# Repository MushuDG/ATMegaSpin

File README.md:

> [!WARNING]  
> Hey! This project is still a Work in Progress. Files, instructions, and other stuff might change!

# Table of contents
1. [Goal of the game](#goal-of-the-game)
2. [PCB Pictures](#pcb-pictures)
    1. [Front](#front)
    2. [Back](#back)
3. [Schematics](#schematics)
    1. [Electrical schematic](#electrical-schematic)
    2. [PCB schematic](#pcb-schematic)
    3. [Mechanical schematic](#mechanical-schematic)
    4. [ATMega328P Pinout](#atmega328p-pinout)
4. [GERBER - 3D printed Files - Other Hardware stuff](#gerber---3d-printed-files---other-hardware-stuff)
    1. [3D Printed parts](#3d-printed-parts)
    2. [PCB GERBER File](#pcb-gerber-file)
    3. [Electrical parts](#electrical-parts)
5. [Installation](#installation)
    1. [Burn bootloader](#burn-bootloader)
        1. [Needed tools](#needed-tools)
        2. [Circuit](#circuit)
        3. [Pinout](#pinout)
        4. [Upload ISP sketch](#upload-isp-sketch)
        5. [Burn bootloader](#burn-bootloader-1)
            1. [Installing Mini-core](#installing-mini-core)
            2. [Select your device, crystal and programmer and burn bootloader](#select-your-device-crystal-and-programmer-and-burn-bootloader)
    2. [Upload sketch from programmer](#upload-sketch-from-programmer)
6. [Contributions](#contributions)
7. [License](#license)

# ATMegaSpin
## Goal of the game:
A LED game where the player has to press a button at the right moment to reach a specific goal. The challenge of the game lies in the speed at which the LEDs blink, the reduction of this speed with each achieved goal, and the necessity to press the button at the right moment to advance in the game.

## PCB Pictures:
### Front

### Back

# Schematics
## Electrical schematic:
[Electrical schematic](https://github.com/MushuDG/ATMegaSpin/blob/main/PDF/ATMegaSpin_Schematic.pdf)

## PCB schematic:
[PCB schematic](https://github.com/MushuDG/ATMegaSpin/blob/main/PDF/ATMegaSpin_PCB.pdf)

## Mechanical schematic:
[Mechanical schematic](https://github.com/MushuDG/ATMegaSpin/blob/main/PDF/EnsemblePCB.pdf)

## ATMega328P Pinout:
| Arduino Pinout | Electrical Part | ATMega328 Pinout | ATMega328 Pinout | Electrical Part | Arduino Pinout |
| -------------- | --------------- | ---------------- | ---------------- | --------------- | -------------- |
| Reset          | Not used        | 1                | 28               | Not used        | A5             |
| D0 RX          | Not used        | 2                | 27               | Not used        | A4             |
| D1 TX          | Not used        | 3                | 26               | Not used        | A3             |
| D2             | LED 1           | 4                | 25               | Not used        | A2             |
| D3             | Button Pin 4    | 5                | 24               | Not used        | A1             |
| D4             | LED 2           | 6                | 23               | Not used        | A0             |
| VCC            | +5V             | 7                | 22               | GND             | GND            |
| GND            | GND             | 8                | 21               | Not used        | Aref           |
| Crystal        | Crystal         | 9                | 20               | Not used        | Avcc           |
| Crystal        | Crystal         | 10               | 19               | LED 10          | D13            |
| D5             | Not used        | 11               | 18               | LED 9           | D12            |
| D6             | LED 3           | 12               | 17               | LED 8           | D11            |
| D7             | LED 4           | 13               | 16               | LED 7           | D10            |
| D8             | LED 5           | 14               | 15               | LED 6           | D9             |

# GERBER - 3D printed Files - Other Hardware stuff
## 3D Printed parts:
[3D Printed parts](https://www.printables.com/fr/model/649943-atmegaspin)

## PCB GERBER File:
[PCB GERBER File](https://github.com/MushuDG/ATMegaSpin/blob/main/KiCad/ATMegaSpin/ATMegaSpin-GERBER.zip)

## Electrical parts:
| N° | PRODUCTS DETAILS                                                                                | SUPPLIER | QUANTITY | PRICE       | TOTAL        |
| -- | ----------------------------------------------------------------------------------------------- | -------- | -------- | ----------- | ------------ |
| 1  | ED3050-5-ND‎<br>ED281DT‎<br>CONN IC DIP SOCKET 28POS TIN                                        | Digikey  | 5        | Fr. 0.40000 | Fr. 2.00000  |
| 2  | ATMEGA328P-PU-ND‎‎<br>ATMEGA328P-PU‎<br>IC MCU 8BIT 32KB FLASH 28DIP                            | Digikey  | 5        | Fr. 2.60000 | Fr. 13.00000 |
| 3  | 2223-TS02-66-60-BK-160-SCR-D-ND‎<br>TS02-66-60-BK-160-SCR-D‎<br>6 X 6 MM, 6 MM ACTUATOR HEIGHT, | Digikey  | 5        | Fr. 0.09000 | Fr. 0.45000  |
| 4  | 50-ECS-160-18-4X-CKM-ND‎<br>ECS-160-18-4X-CKM‎<br>CRYSTAL 16.0000MHZ 18PF TH                    | Digikey  | 5        | Fr. 0.41000 | Fr. 2.05000  |
| 5  | BC1005CT-ND‎<br>‎K220J15C0GF5TL2‎<br>CAP CER 22PF 50V C0G/NP0 RADIAL                            | Digikey  | 10       | Fr. 0.15500 | Fr. 1.55000  |
| 6  | BS-7-ND‎<br>BS-7‎<br>BATT HLDR COIN 20MM 1 CEL PC PIN                                           | Digikey  | 10       | Fr. 0.84100 | Fr. 8.41000  |
| 7  | CF18JT200RCT-ND‎<br>‎CF18JT200R‎<br>RES 200 OHM 5% 1/8W AXIAL                                   | Digikey  | 50       | Fr. 0.02260 | Fr. 1.13000  |
| 8  | ‎516-1325-ND‎<br>‎HLMP-4700‎<br>LED RED DIFFUSED T-1 3/4 T/H                                    | Digikey  | 50       | Fr. 0.34600 | Fr. 17.30000 |
| 9  | MFS101D-6-Z                                                                                     | Digikey  | 5        | Fr. 1.52000 | Fr. 7.60000  |
| 10 | PCB JLCPCB                                                                                      | JLCPCB   | 5        | Fr. 1.84000 | Fr. 9.20000  |
|    |                                                                                                 |          |          |             |              |
|    | Aprox. Total                                                                                    |          |          |             | Fr. 62.69    |
|    | Aprox. Total/pcs                                                                                |          |          |             | Fr. 12.54    |

# Prototype

# Installation
Before you can connect the [ATMega328P](https://en.wikipedia.org/wiki/ATmega328) microcontroller to the circuit, it's necessary to burn the bootloader of the chip. Once the bootloader is burned, the program can be uploaded to it.

*"To program the bootloader and provide to the microcontroller the compatibility with the Arduino Software (IDE) you need to use an In-circuit Serial Programmer (ISP) that is the device that connects to a specific set of pins of the microcontroller to perform the programming of the whole flash memory of the microcontroller, bootloader included. The ISP programming procedure also includes the writing of fuses: a special set of bits that define how the microcontroller works under specific circumstances."*

The Memory Map of an ATmega328P

> [!IMPORTANT]  
> The preceding paragraph and illustration were taken from this documentation: [Arduino as ISP and Arduino Bootloaders](https://docs.arduino.cc/built-in-examples/arduino-isp/ArduinoISP) -  Accessed on 2023-11-22

## Burn bootloader
### Needed tools
To burn the bootloader on the microcontroller you need 2 arduino (In this case I use Arduino UNO) cards. The first will be used as an ISP programmer.

### Circuit

### Pinout
| Arduino Programmer Pin | Arduino Target Pin |
| ---------------------- | ------------------ |
| +5 [V]                 | +5 [V]             |
| GND                    | GND                |
| D10                    | Reset              |
| 11                     | 11                 |
| 12                     | 12                 |
| 13                     | 13                 |

### Upload ISP sketch
Once the circuit is connected, follow the following instructions to apply the ISP programming sketch on the Arduino programmer:
1. Open the Arduino IDE and from the menu *File > Examples > 11.ArduinoISP > ArduinoISP*, load the sketch.
2. Select the proper board (I.E.: Arduino Uno) and upload the sketch

### Burn bootloader
#### Installing Mini-core
1. Open up the Arduino IDE and navigate to the preferences (or press ctrl+,). Copy the following URL into the empty field labelled *‘Additional Boards Manager URLs’*: [https://mcudude.github.io/MiniCore/package_MCUdude_MiniCore_index.json](https://mcudude.github.io/MiniCore/package_MCUdude_MiniCore_index.json)
2. Go to the boards manager, which can be found under *Tools > Board > Boards Manager*.
Type *‘minicore’* into the search bar and the relevant entry will appear. Select the latest version and click *‘install’*. Once the installation is complete, close the boards manager window.

#### Select your device, crystal and programmer and burn bootloader
1. Select the relevant device, crystal and programmer options under the *‘tools’* menu.
2. Under board, select *‘ATmega328’* (or whichever chip you’re using).
3. Under clock, select the frequency of your external clock. It should be written in block capitals on the top of the crystal’s casing.
4. Set your programmer as *‘Arduino as ISP’*
5. Burn the bootloader using the *‘Burn Bootloader’* option at the bottom of the Tools menu.

## Upload sketch from programmer
Once the bootloader is burned, open up the *[Spin.ino](https://github.com/MushuDG/ATMegaSpin/blob/main/Code/Spin/Spin.ino)* sketch. From the menu *Sketch* use the *Upload Using Programmer* tool to Upload the sketch to the ATMega328P Target.

Then, you can disconnect the MCU from the Arduino target and clip it to your circuit. 

## Contributions

Contributions to this project are welcome! If you have ideas for improvements or bug fixes, please follow the [contribution guidelines](CONTRIBUTING.md).

1. Fork the project.
2. Create your feature branch: `git checkout -b feature/AmazingFeature`.
3. Commit your changes: `git commit -m 'Add some amazing feature'`.
4. Push to the branch: `git push origin feature/AmazingFeature`.
5. Open a pull request.

## License

This project is licensed under the  AGPL-3.0 license - see the [LICENSE](LICENSE) file for details.

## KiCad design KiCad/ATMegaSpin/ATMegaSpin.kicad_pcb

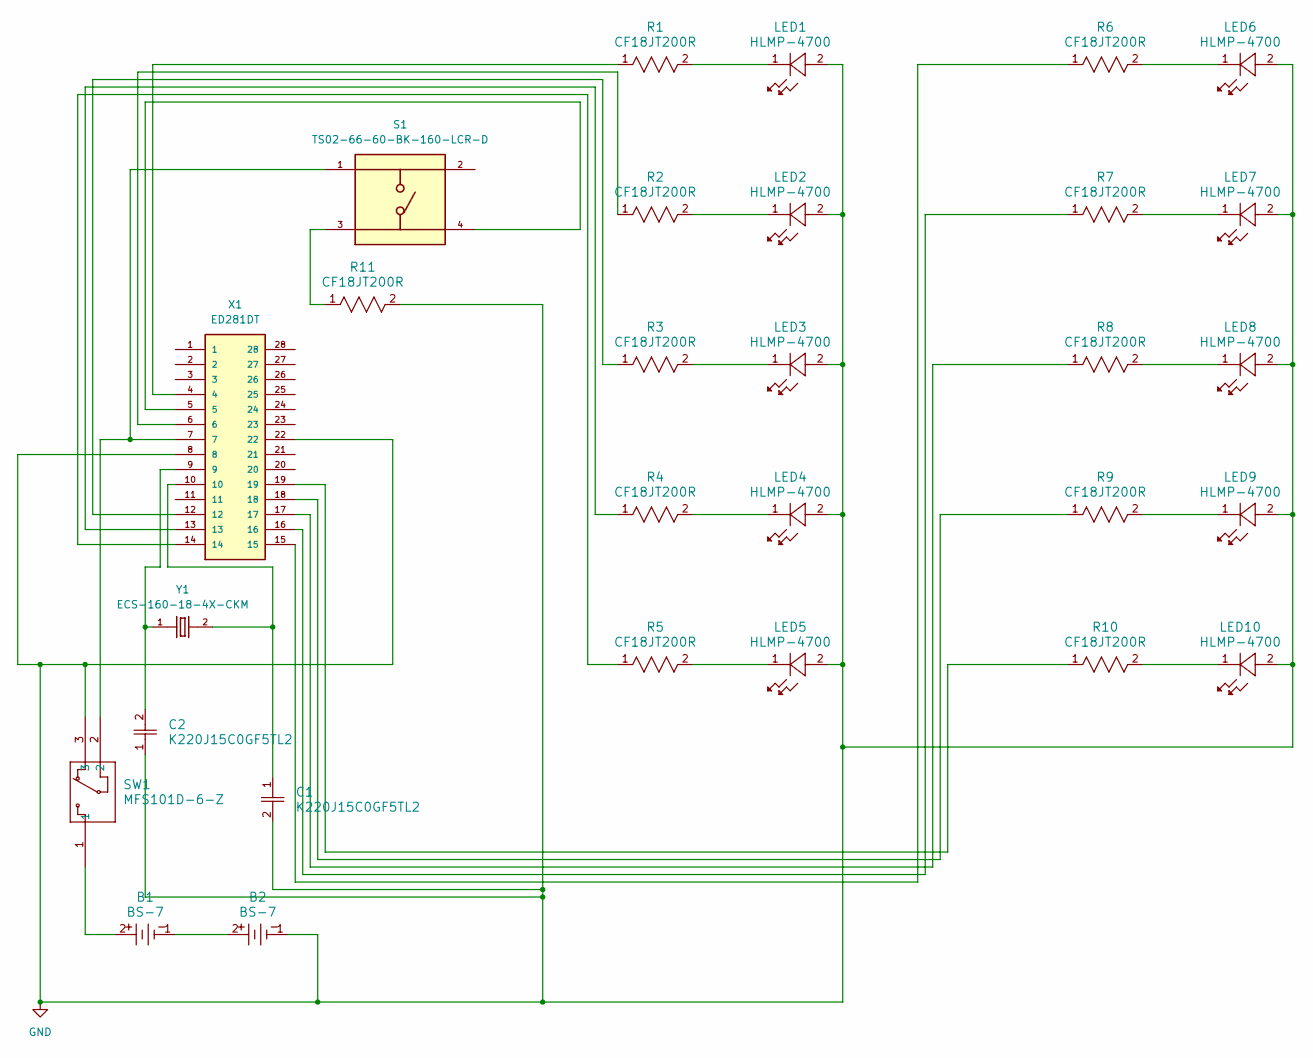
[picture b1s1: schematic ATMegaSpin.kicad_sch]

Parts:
B1, B2: BS-7; BS-7_MPD
C1, C2: K220J15C0GF5TL2; CAP_K-SERIES_15-L2_VIS
LED1, LED2, LED3, LED4, LED5, LED6, LED7, LED8, LED9, LED10: HLMP-4700; LED_HLMP-47XX_BRA
R1, R2, R3, R4, R5, R6, R7, R8, R9, R10, R11: CF18JT200R; STA_CF18_STP
S1: TS02-66-60-BK-160-LCR-D; SW_TS02-66-60-BK-160-LCR-D; PARTREV 1.0
SW1: MFS101D-6-Z; MFS101D-6-Z_NDC
X1: ED281DT; OST_ED281DT; PARTREV D
Y1: ECS-160-18-4X-CKM; XTAL_ECS-160-18-4X-CKM

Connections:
GND: B2.1, C1.2, C2.1, LED1.2, LED2.2, LED3.2, LED4.2, LED5.2, LED6.2, LED7.2, LED8.2, LED9.2, LED10.2, R11.2, SW1.3, X1.8, X1.22
unnamed: B1.1, B2.2
unnamed: B1.2, SW1.1
unnamed: C1.1, X1.10, Y1.2
unnamed: C2.2, X1.9, Y1.1
unnamed: LED1.1, R1.2
unnamed: LED2.1, R2.2
unnamed: LED3.1, R3.2
unnamed: LED4.1, R4.2
unnamed: LED5.1, R5.2
unnamed: LED6.1, R6.2
unnamed: LED7.1, R7.2
unnamed: LED8.1, R8.2
unnamed: LED9.1, R9.2
unnamed: LED10.1, R10.2
unnamed: R1.1, X1.4
unnamed: R2.1, X1.6
unnamed: R3.1, X1.12
unnamed: R4.1, X1.13
unnamed: R5.1, X1.14
unnamed: R6.1, X1.15
unnamed: R7.1, X1.16
unnamed: R8.1, X1.17
unnamed: R9.1, X1.18
unnamed: R10.1, X1.19
unnamed: R11.1, S1.3
unnamed: S1.1, SW1.2, X1.7
unnamed: S1.4, X1.5

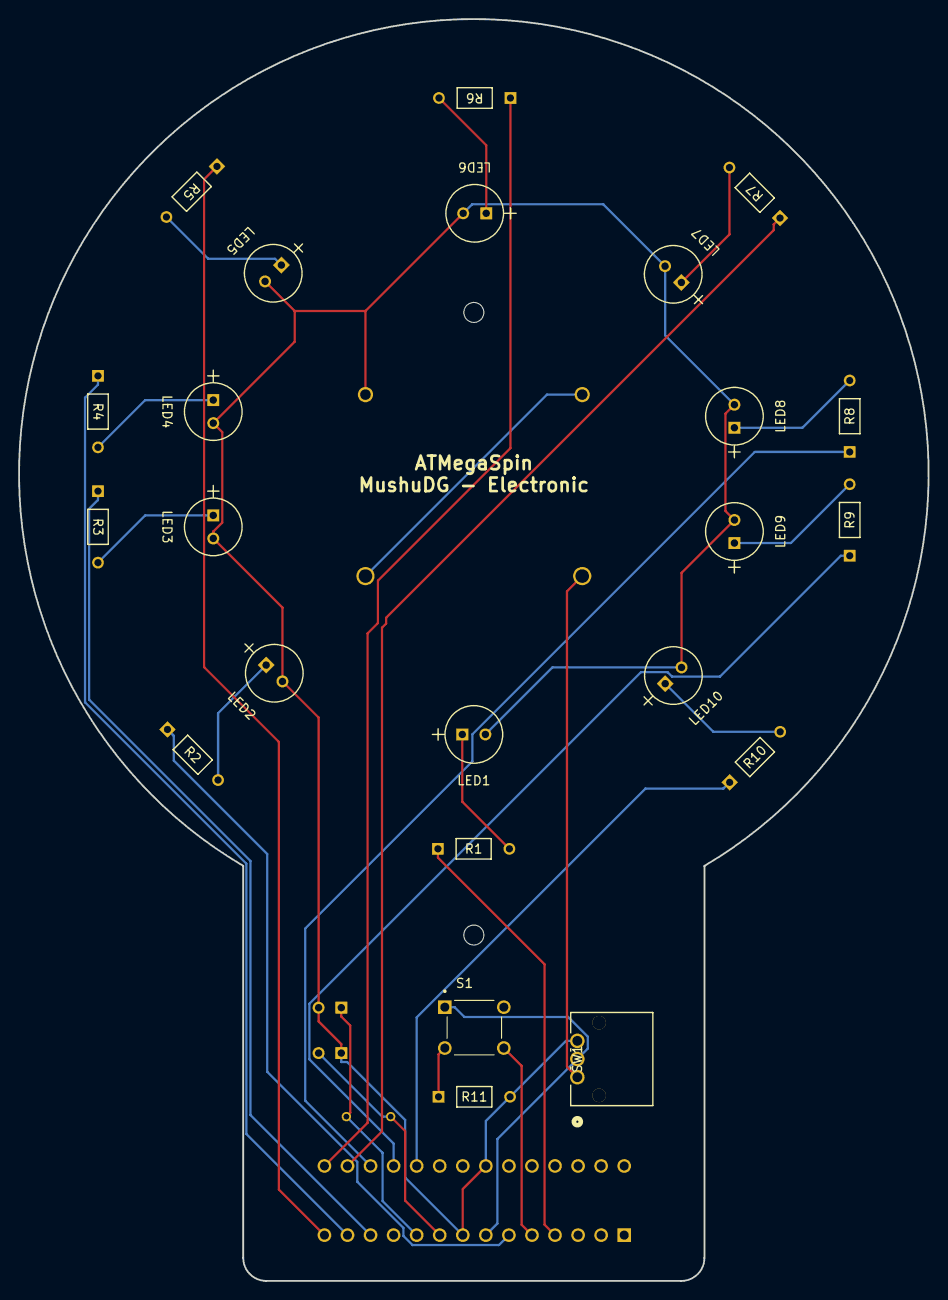
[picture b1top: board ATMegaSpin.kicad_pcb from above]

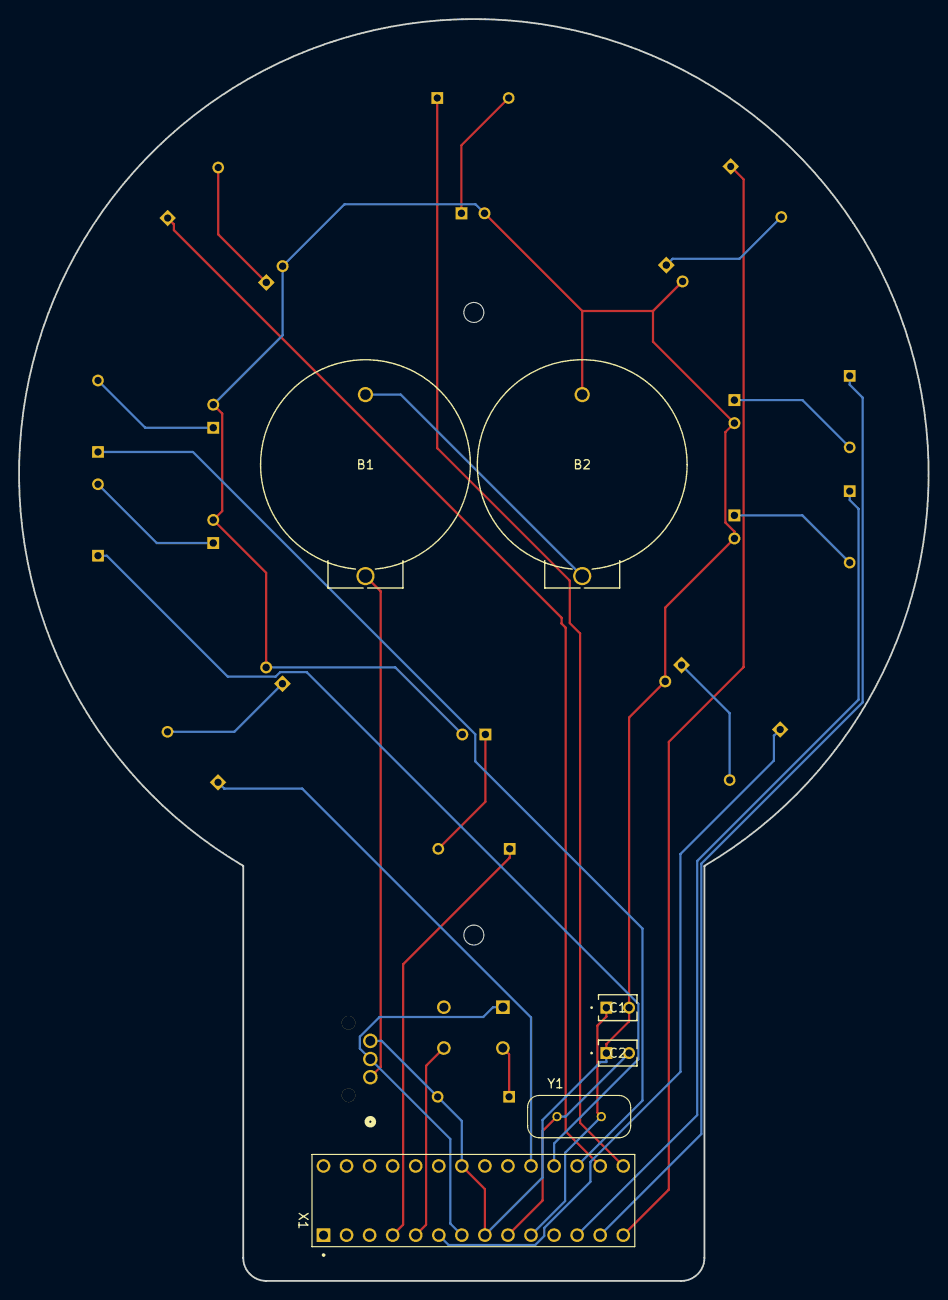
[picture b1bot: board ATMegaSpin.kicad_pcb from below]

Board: 2 copper layers, 100.2 x 139.0 mm, 31 parts (6 on the bottom side), 28 nets.

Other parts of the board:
H: MountingHole_2.2mm_M2
h2: MountingHole_2.2mm_M2

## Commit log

2023-11-14 Create LICENSE
2023-11-14 Update code
2023-11-14 Add KiCad files
2023-11-15 Update KiCad files
2023-11-15 Adapt tree
2023-11-15 Kicad updated
2023-11-15 Update Kicad
2023-11-15 Adjust speed
2023-11-16 Update CAD
2023-11-17 Manage Tree
2023-11-17 Modify Inventor Files
2023-11-17 Update invntor
2023-11-20 Modify box
2023-11-22 Update Box
2023-11-22 Change folder Name
2023-11-22 Update pictures
2023-11-22 Upload Readme
2023-11-22 Modify image
2023-11-22 Update files
2023-11-22 Test Table of contents
2023-11-22 Update README + 3D Pictures view
2023-11-22 Update 3D View
2023-11-22 Update 3D View + schematic + GERBER files
2023-11-22 Enable Release 1.0.0-beta
2023-11-23 Update algorithm
2023-12-05 Replace Delay by Millis()
2023-12-05 Update documentation
2023-12-06 Optimising Code
2023-12-12 Debug
2023-12-14 Update prototype picture
2023-12-19 Edit algo
2024-01-26 👌 IMPROVE: Modifying the box
